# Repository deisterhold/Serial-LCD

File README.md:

Serial-LCD
==========

Controlling a 16x2 LCD using an ATtiny85 & 74HC595 Shift Register

Necessary Items:

16x2 LCD Display, 
ATtiny85 Microcontroller with Programmer, 
74HC595 Shift Register, 
NPN Transistor, 
10K Potentiometer, 
Jumper Wires & Breadboard

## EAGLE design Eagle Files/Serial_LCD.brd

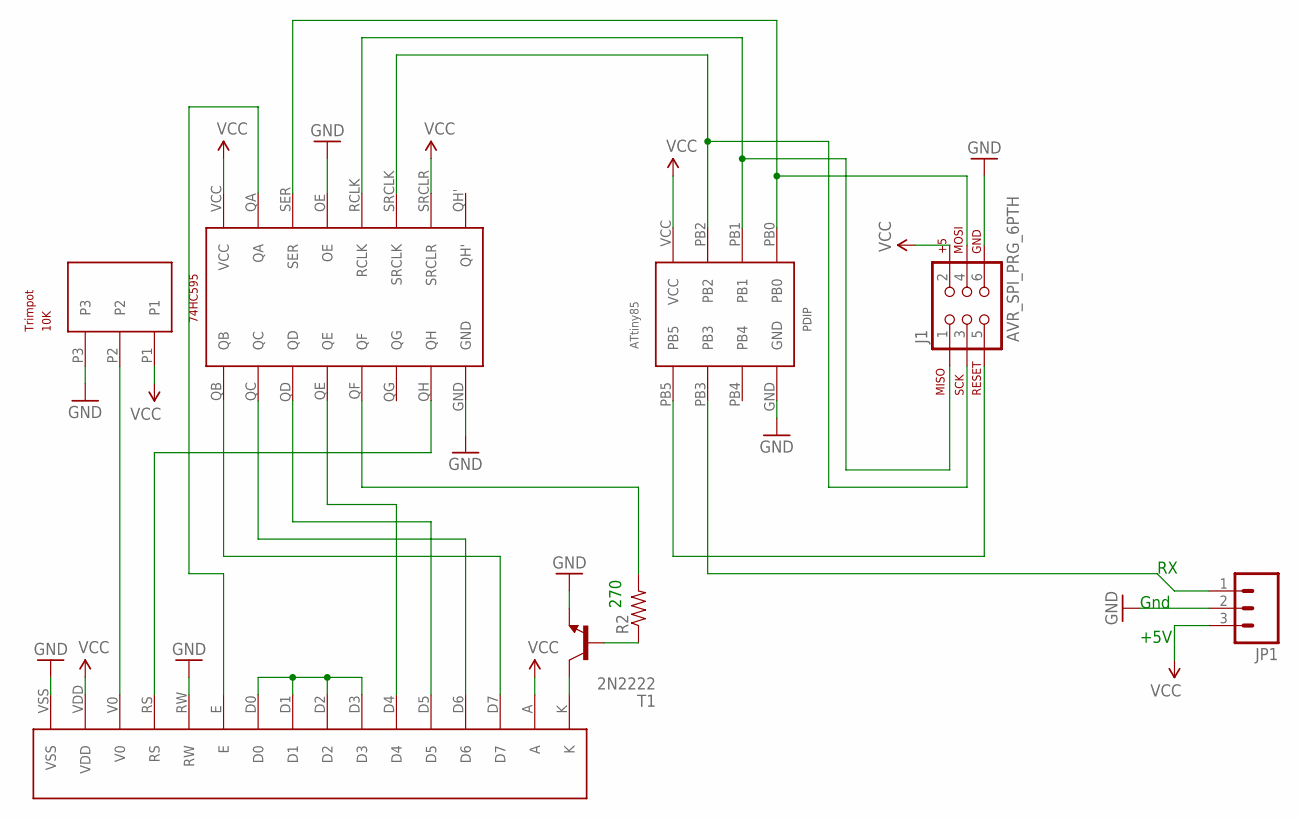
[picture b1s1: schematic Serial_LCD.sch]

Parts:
J1: AVR_SPI_PRG_6PTH; 2X3
JP1: M03PTH; 1X03
R1: TRIMPOT-3386P
R2: RESISTORPTH-1/4W; AXIAL-0.4
T1: 2N2222; TO92-EBC-OVAL
U1: SN74HC595N
U2: ATTINY85-20PU
U$1: 16X2_LCD

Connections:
GND: J1.6, JP1.2, R1.P3, T1.E, U1.GND, U1.OE, U2.GND, U$1.RW, U$1.VSS
unnamed: R1.P2, U$1.V0
unnamed: R2.P$1 (1), T1.B
unnamed: T1.C, U$1.K
unnamed: J1.4, U1.SER, U2.PB0
unnamed: U1.QB, U$1.D7
unnamed: U1.QC, U$1.D6
unnamed: U1.QD, U$1.D5
unnamed: U1.QE, U$1.D4
unnamed: R2.P$2 (2), U1.QF
unnamed: U$1.D0, U$1.D1, U$1.D2, U$1.D3
unnamed: U1.QH, U$1.RS
unnamed: U1.QA, U$1.E
unnamed: J1.1, U1.RCLK, U2.PB1
unnamed: J1.3, U1.SRCLK, U2.PB2
unnamed: J1.5, U2.PB5
unnamed: JP1.1, U2.PB3
VCC: J1.2, JP1.3, R1.P1, U1.SRCLR, U1.VCC, U2.VCC, U$1.A, U$1.VDD

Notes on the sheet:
270
Gnd
+5V

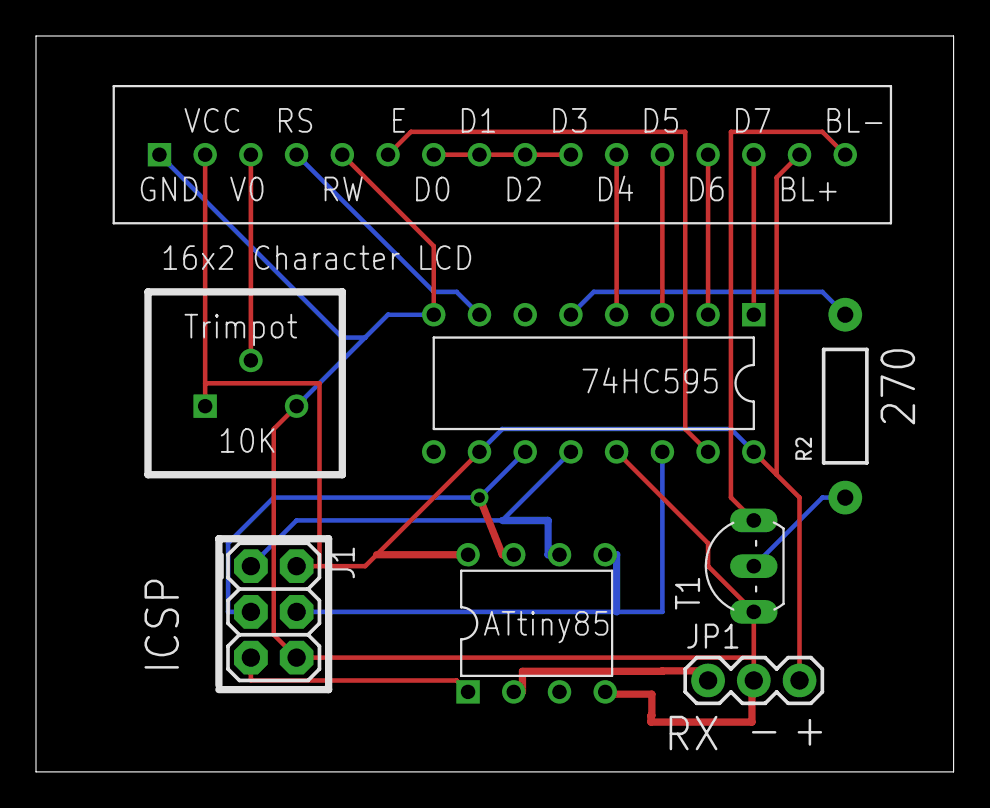
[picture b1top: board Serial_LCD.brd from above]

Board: 2 copper layers, 51.0 x 40.9 mm, 8 parts (0 on the bottom side), 18 nets.

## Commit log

2014-02-19 Arduino Code
    Version 1.0
2014-02-19 Splash Screen
    Changed Splash to screen to allow Arduino to boot.
2014-02-19 3D Models
    Added Google Sketchup Files of the different components
2014-02-20 Transferred to different Repository
    3D files moved to Arduino-Phone Repo
2014-02-24 Added Eagle Board Files
    First Version of the PCB version
2014-02-24 test
2014-02-24 Updated Eagle Files
2014-04-15 Changed Power on Information
    Adjusted what is displayed on the LCD when powered on.

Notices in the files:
parts and their libraries:
SparkFun-Connectors: Licensing: Creative Commons ShareAlike 4.0 International - https://creativecommons.org/licenses/by-sa/4.0
